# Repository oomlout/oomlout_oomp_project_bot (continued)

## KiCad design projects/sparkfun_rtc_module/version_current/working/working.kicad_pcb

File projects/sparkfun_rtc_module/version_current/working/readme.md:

# RTC-Module by sparkfun  
This is a harvested standardized copy of a project from github.  
The original project can be found at:  
https://github.com/sparkfun/RTC-Module  
Please consult that link for additional, details, files, and license information.  
Note: It was auto harvested and if the original repo had more than one board file or anything out of the ordinary the files here are likely not representative.

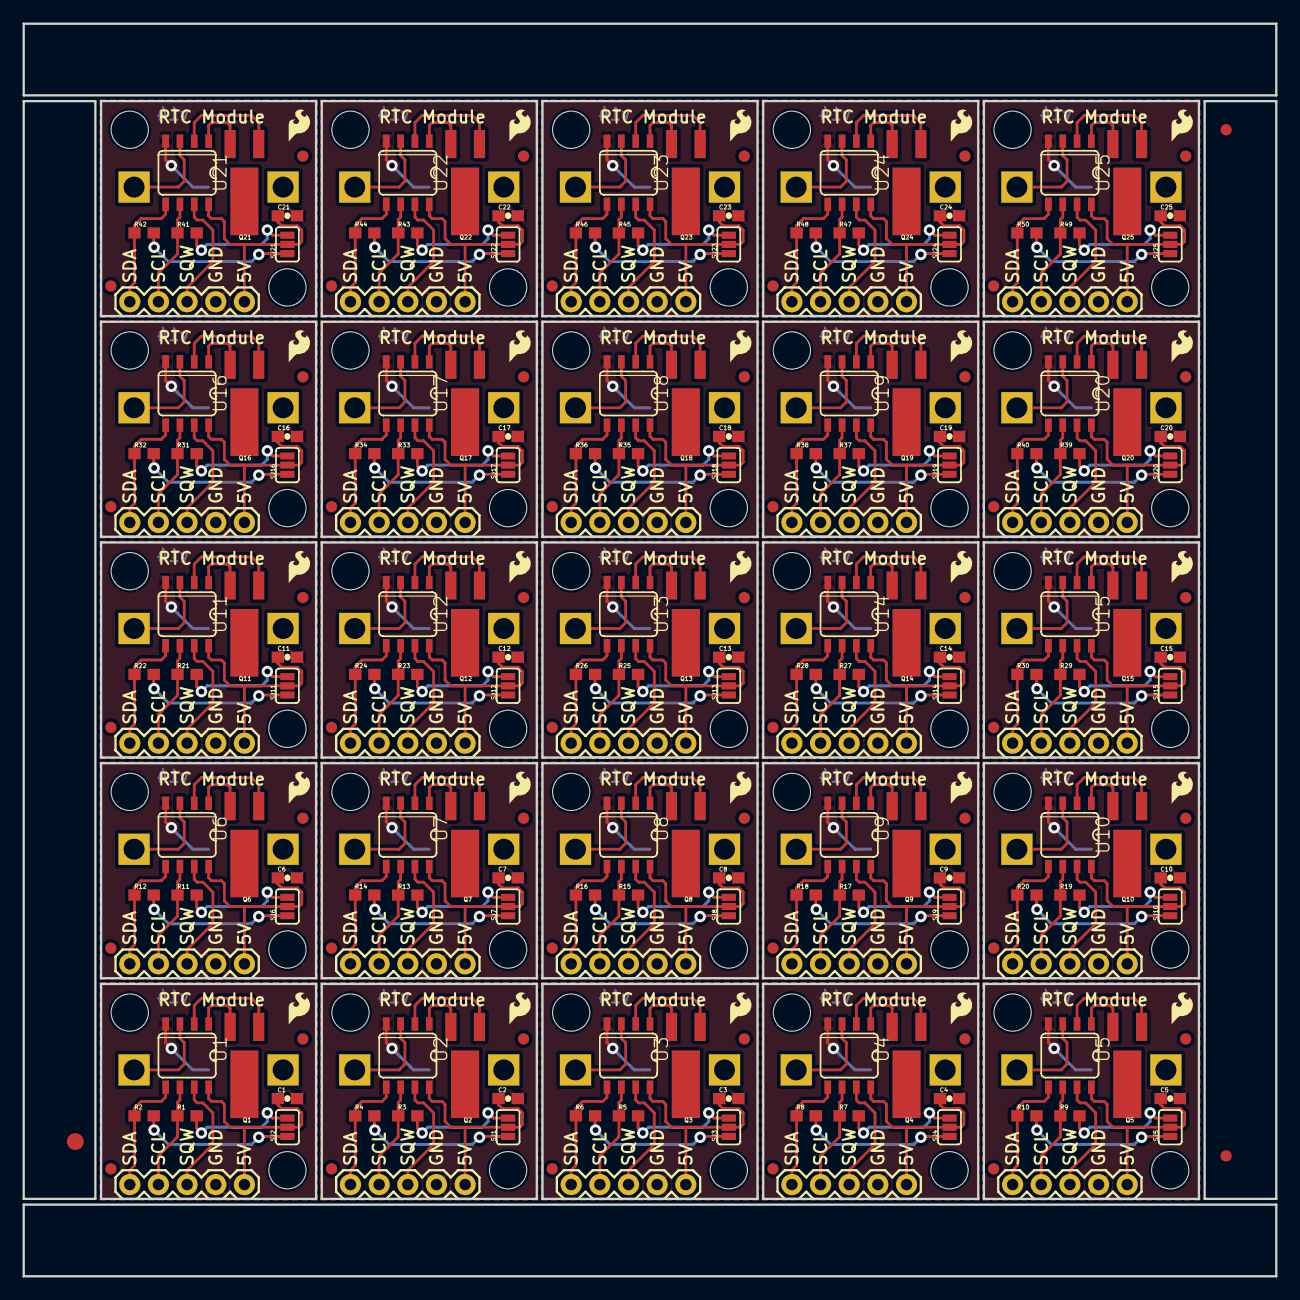
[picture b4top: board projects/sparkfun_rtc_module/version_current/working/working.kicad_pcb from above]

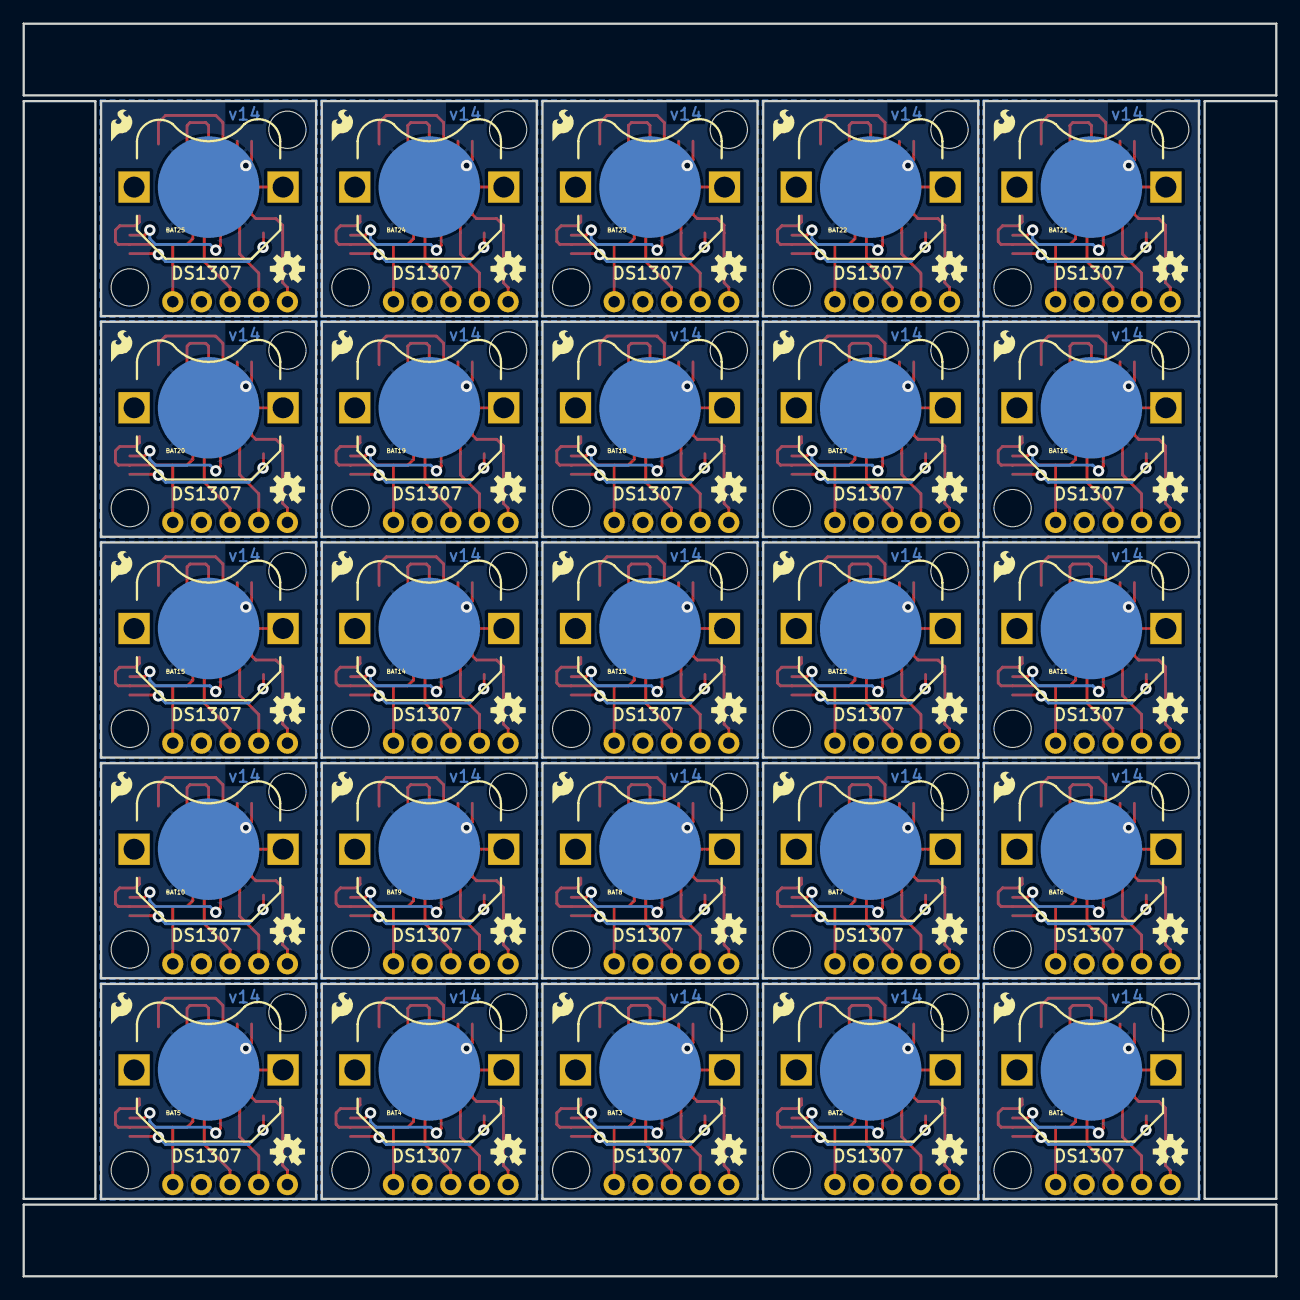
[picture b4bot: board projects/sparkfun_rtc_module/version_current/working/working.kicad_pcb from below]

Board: 2 copper layers, 111.0 x 111.0 mm, 378 parts (75 on the bottom side), 250 nets.

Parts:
BAT1, BAT2, BAT3, BAT4, BAT5, BAT6, BAT7, BAT8, BAT9, BAT10, BAT11, BAT12, BAT13, BAT14, BAT15, BAT16, BAT17, BAT18, BAT19, BAT20, BAT21, BAT22, BAT23, BAT24, BAT25: BATTCON_12MM_PTH
C1, C2, C3, C4, C5, C6, C7, C8, C9, C10, C11, C12, C13, C14, C15, C16, C17, C18, C19, C20, C21, C22, C23, C24, C25: 0.1uF; 0603-CAP
E$1, E$2, E$3, E$4, E$5, E$6, E$7, E$8, E$9, E$10, E$11, E$12, E$13, E$14, E$15, E$16, E$17, E$18, E$19, E$20, E$21, E$22, E$23, E$24, E$25, E$26, E$27, E$28, E$29, E$30, E$31, E$32, E$33, E$34, E$35, E$36, E$37, E$38, E$39, E$40, E$41, E$42, E$43, E$44, E$45, E$46, E$47, E$48, E$49, E$50, E$54, E$55: FIDUCIAL-1X2
E$51: FIDUCIAL-1.5X3
JP1, JP2, JP3, JP4, JP5, JP6, JP7, JP8, JP9, JP10, JP11, JP12, JP13, JP14, JP15, JP16, JP17, JP18, JP19, JP20, JP21, JP22, JP23, JP24, JP25: 1X05
LOGO1, LOGO2, LOGO3, LOGO4, LOGO5, LOGO6, LOGO7, LOGO8, LOGO9, LOGO10, LOGO11, LOGO12, LOGO13, LOGO14, LOGO15, LOGO16, LOGO17, LOGO18, LOGO19, LOGO20, LOGO21, LOGO22, LOGO23, LOGO24, LOGO25: OSHW-LOGOS; OSHW-LOGO-S
Q1, Q2, Q3, Q4, Q5, Q6, Q7, Q8, Q9, Q10, Q11, Q12, Q13, Q14, Q15, Q16, Q17, Q18, Q19, Q20, Q21, Q22, Q23, Q24, Q25: 32.768kHz; CRYSTAL-32KHZ-SMD
R1, R2, R3, R4, R5, R6, R7, R8, R9, R10, R11, R12, R13, R14, R15, R16, R17, R18, R19, R20, R21, R22, R23, R24, R25, R26, R27, R28, R29, R30, R31, R32, R33, R34, R35, R36, R37, R38, R39, R40, R41, R42, R43, R44, R45, R46, R47, R48, R49, R50: 4.7k; 0603
SJ1, SJ2, SJ3, SJ4, SJ5, SJ6, SJ7, SJ8, SJ9, SJ10, SJ11, SJ12, SJ13, SJ14, SJ15, SJ16, SJ17, SJ18, SJ19, SJ20, SJ21, SJ22, SJ23, SJ24, SJ25: SJ_3_PASTE1&2&3
U1, U2, U3, U4, U5, U6, U7, U8, U9, U10, U11, U12, U13, U14, U15, U16, U17, U18, U19, U20, U21, U22, U23, U24, U25: DS1307; SO08-TIGHT
U$1, U$2, U$3, U$8, U$9, U$12, U$13, U$16, U$17, U$20, U$21, U$24, U$25, U$28, U$29, U$32, U$33, U$36, U$37, U$40, U$41, U$44, U$45, U$48, U$49, U$52, U$53, U$56, U$57, U$60, U$61, U$64, U$65, U$68, U$69, U$72, U$73, U$76, U$77, U$80, U$81, U$84, U$85, U$88, U$89, U$92, U$93, U$96, U$97, U$100: LOGO-SFESK; SFE-LOGO-FLAME
U$4, U$5, U$6, U$7, U$10, U$11, U$14, U$15, U$18, U$19, U$22, U$23, U$26, U$27, U$30, U$31, U$34, U$35, U$38, U$39, U$42, U$43, U$46, U$47, U$50, U$51, U$54, U$55, U$58, U$59, U$62, U$63, U$66, U$67, U$70, U$71, U$74, U$75, U$78, U$79, U$82, U$83, U$86, U$87, U$90, U$91, U$94, U$95, U$98, U$99: STAND-OFF

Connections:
5V: C1.1, JP1.1, SJ2.2, U1.8
5V1: C2.1, JP2.1, SJ1.2, U2.8
5V2: C3.1, JP3.1, SJ3.2, U3.8
5V3: C4.1, JP4.1, SJ4.2, U4.8
5V4: C5.1, JP5.1, SJ5.2, U5.8
5V5: C6.1, JP6.1, SJ6.2, U6.8
5V6: C7.1, JP7.1, SJ7.2, U7.8
5V7: C8.1, JP8.1, SJ8.2, U8.8
5V8: C9.1, JP9.1, SJ9.2, U9.8
5V9: C10.1, JP10.1, SJ10.2, U10.8
5V10: C11.1, JP11.1, SJ11.2, U11.8
5V11: C12.1, JP12.1, SJ12.2, U12.8
5V12: C13.1, JP13.1, SJ13.2, U13.8
5V13: C14.1, JP14.1, SJ14.2, U14.8
5V14: C15.1, JP15.1, SJ15.2, U15.8
5V15: C16.1, JP16.1, SJ16.2, U16.8
5V16: C17.1, JP17.1, SJ17.2, U17.8
5V17: C18.1, JP18.1, SJ18.2, U18.8
5V18: C19.1, JP19.1, SJ19.2, U19.8
5V19: C20.1, JP20.1, SJ20.2, U20.8
5V20: C21.1, JP21.1, SJ21.2, U21.8
5V21: C22.1, JP22.1, SJ22.2, U22.8
5V22: C23.1, JP23.1, SJ23.2, U23.8
5V23: C24.1, JP24.1, SJ24.2, U24.8
5V24: C25.1, JP25.1, SJ25.2, U25.8
GND: BAT1.GND, C1.2, JP1.2, U1.4
GND1: BAT2.GND, C2.2, JP2.2, U2.4
GND2: BAT3.GND, C3.2, JP3.2, U3.4
GND3: BAT4.GND, C4.2, JP4.2, U4.4
GND4: BAT5.GND, C5.2, JP5.2, U5.4
GND5: BAT6.GND, C6.2, JP6.2, U6.4
GND6: BAT7.GND, C7.2, JP7.2, U7.4
GND7: BAT8.GND, C8.2, JP8.2, U8.4
GND8: BAT9.GND, C9.2, JP9.2, U9.4
GND9: BAT10.GND, C10.2, JP10.2, U10.4
GND10: BAT11.GND, C11.2, JP11.2, U11.4
GND11: BAT12.GND, C12.2, JP12.2, U12.4
GND12: BAT13.GND, C13.2, JP13.2, U13.4
GND13: BAT14.GND, C14.2, JP14.2, U14.4
GND14: BAT15.GND, C15.2, JP15.2, U15.4
GND15: BAT16.GND, C16.2, JP16.2, U16.4
GND16: BAT17.GND, C17.2, JP17.2, U17.4
GND17: BAT18.GND, C18.2, JP18.2, U18.4
GND18: BAT19.GND, C19.2, JP19.2, U19.4
GND19: BAT20.GND, C20.2, JP20.2, U20.4
GND20: BAT21.GND, C21.2, JP21.2, U21.4
GND21: BAT22.GND, C22.2, JP22.2, U22.4
GND22: BAT23.GND, C23.2, JP23.2, U23.4
GND23: BAT24.GND, C24.2, JP24.2, U24.4
GND24: BAT25.GND, C25.2, JP25.2, U25.4
unnamed: Q1.X2, U1.1
unnamed: Q1.X1, U1.2
unnamed: Q2.X2, U2.1
unnamed: BAT1.VCC@1, U1.3
unnamed: R1.2, SJ2.3
unnamed: R2.2, SJ2.1
unnamed: Q2.X1, U2.2
unnamed: BAT2.VCC@1, U2.3
unnamed: R3.2, SJ1.3
unnamed: R4.2, SJ1.1
unnamed: Q3.X2, U3.1
unnamed: Q3.X1, U3.2
unnamed: BAT3.VCC@1, U3.3
unnamed: R5.2, SJ3.3
unnamed: R6.2, SJ3.1
unnamed: Q4.X2, U4.1
unnamed: Q4.X1, U4.2
unnamed: BAT4.VCC@1, U4.3
unnamed: R7.2, SJ4.3
unnamed: R8.2, SJ4.1
unnamed: Q5.X2, U5.1
unnamed: Q5.X1, U5.2
unnamed: BAT5.VCC@1, U5.3
unnamed: R9.2, SJ5.3
unnamed: R10.2, SJ5.1
unnamed: Q6.X2, U6.1
unnamed: Q6.X1, U6.2
unnamed: BAT6.VCC@1, U6.3
unnamed: R11.2, SJ6.3
unnamed: R12.2, SJ6.1
unnamed: Q7.X2, U7.1
unnamed: Q7.X1, U7.2
unnamed: BAT7.VCC@1, U7.3
unnamed: R13.2, SJ7.3
unnamed: R14.2, SJ7.1
unnamed: Q8.X2, U8.1
unnamed: Q8.X1, U8.2
unnamed: BAT8.VCC@1, U8.3
unnamed: R15.2, SJ8.3
unnamed: R16.2, SJ8.1
unnamed: Q9.X2, U9.1
unnamed: Q9.X1, U9.2
unnamed: BAT9.VCC@1, U9.3
unnamed: R17.2, SJ9.3
unnamed: R18.2, SJ9.1
unnamed: Q10.X2, U10.1
unnamed: Q10.X1, U10.2
unnamed: BAT10.VCC@1, U10.3
unnamed: R19.2, SJ10.3
unnamed: R20.2, SJ10.1
unnamed: Q11.X2, U11.1
unnamed: Q11.X1, U11.2
unnamed: BAT11.VCC@1, U11.3
unnamed: R21.2, SJ11.3
unnamed: R22.2, SJ11.1
unnamed: Q12.X2, U12.1
unnamed: Q12.X1, U12.2
unnamed: BAT12.VCC@1, U12.3
unnamed: R23.2, SJ12.3
unnamed: R24.2, SJ12.1
unnamed: Q13.X2, U13.1
unnamed: Q13.X1, U13.2
unnamed: BAT13.VCC@1, U13.3
unnamed: R25.2, SJ13.3
unnamed: R26.2, SJ13.1
unnamed: Q14.X2, U14.1
unnamed: Q14.X1, U14.2
unnamed: BAT14.VCC@1, U14.3
unnamed: R27.2, SJ14.3
unnamed: R28.2, SJ14.1
unnamed: Q15.X2, U15.1
unnamed: Q15.X1, U15.2
unnamed: BAT15.VCC@1, U15.3
unnamed: R29.2, SJ15.3
unnamed: R30.2, SJ15.1
unnamed: Q16.X2, U16.1
unnamed: Q16.X1, U16.2
unnamed: BAT16.VCC@1, U16.3
unnamed: R31.2, SJ16.3
unnamed: R32.2, SJ16.1
unnamed: Q17.X2, U17.1
unnamed: Q17.X1, U17.2
unnamed: BAT17.VCC@1, U17.3
unnamed: R33.2, SJ17.3
unnamed: R34.2, SJ17.1
unnamed: Q18.X2, U18.1
unnamed: Q18.X1, U18.2
unnamed: BAT18.VCC@1, U18.3
unnamed: R35.2, SJ18.3
unnamed: R36.2, SJ18.1
unnamed: Q19.X2, U19.1
unnamed: Q19.X1, U19.2
unnamed: BAT19.VCC@1, U19.3
unnamed: R37.2, SJ19.3
unnamed: R38.2, SJ19.1
unnamed: Q20.X2, U20.1
unnamed: Q20.X1, U20.2
unnamed: BAT20.VCC@1, U20.3
unnamed: R39.2, SJ20.3
unnamed: R40.2, SJ20.1
unnamed: Q21.X2, U21.1
unnamed: Q21.X1, U21.2
unnamed: BAT21.VCC@1, U21.3
unnamed: R41.2, SJ21.3
unnamed: R42.2, SJ21.1
unnamed: Q22.X2, U22.1
unnamed: Q22.X1, U22.2
unnamed: BAT22.VCC@1, U22.3
unnamed: R43.2, SJ22.3
unnamed: R44.2, SJ22.1
unnamed: Q23.X2, U23.1
unnamed: Q23.X1, U23.2
unnamed: BAT23.VCC@1, U23.3
unnamed: R45.2, SJ23.3
unnamed: R46.2, SJ23.1
unnamed: Q24.X2, U24.1
unnamed: Q24.X1, U24.2
unnamed: BAT24.VCC@1, U24.3
unnamed: R47.2, SJ24.3
unnamed: R48.2, SJ24.1
unnamed: Q25.X2, U25.1
unnamed: Q25.X1, U25.2
unnamed: BAT25.VCC@1, U25.3
unnamed: R49.2, SJ25.3
unnamed: R50.2, SJ25.1
SCL: JP1.4, R1.1, U1.6
SCL1: JP2.4, R3.1, U2.6
SCL2: JP3.4, R5.1, U3.6
SCL3: JP4.4, R7.1, U4.6
SCL4: JP5.4, R9.1, U5.6
SCL5: JP6.4, R11.1, U6.6
SCL6: JP7.4, R13.1, U7.6
SCL7: JP8.4, R15.1, U8.6
SCL8: JP9.4, R17.1, U9.6
SCL9: JP10.4, R19.1, U10.6
SCL10: JP11.4, R21.1, U11.6
SCL11: JP12.4, R23.1, U12.6
SCL12: JP13.4, R25.1, U13.6
SCL13: JP14.4, R27.1, U14.6
SCL14: JP15.4, R29.1, U15.6
SCL15: JP16.4, R31.1, U16.6
SCL16: JP17.4, R33.1, U17.6
SCL17: JP18.4, R35.1, U18.6
SCL18: JP19.4, R37.1, U19.6
SCL19: JP20.4, R39.1, U20.6
SCL20: JP21.4, R41.1, U21.6
SCL21: JP22.4, R43.1, U22.6
SCL22: JP23.4, R45.1, U23.6
SCL23: JP24.4, R47.1, U24.6
SCL24: JP25.4, R49.1, U25.6
SDA: JP1.5, R2.1, U1.5
SDA1: JP2.5, R4.1, U2.5
SDA2: JP3.5, R6.1, U3.5
SDA3: JP4.5, R8.1, U4.5
SDA4: JP5.5, R10.1, U5.5
SDA5: JP6.5, R12.1, U6.5
SDA6: JP7.5, R14.1, U7.5
SDA7: JP8.5, R16.1, U8.5
SDA8: JP9.5, R18.1, U9.5
SDA9: JP10.5, R20.1, U10.5
SDA10: JP11.5, R22.1, U11.5
SDA11: JP12.5, R24.1, U12.5
SDA12: JP13.5, R26.1, U13.5
SDA13: JP14.5, R28.1, U14.5
SDA14: JP15.5, R30.1, U15.5
SDA15: JP16.5, R32.1, U16.5
SDA16: JP17.5, R34.1, U17.5
SDA17: JP18.5, R36.1, U18.5
SDA18: JP19.5, R38.1, U19.5
SDA19: JP20.5, R40.1, U20.5
SDA20: JP21.5, R42.1, U21.5
SDA21: JP22.5, R44.1, U22.5
SDA22: JP23.5, R46.1, U23.5
SDA23: JP24.5, R48.1, U24.5
SDA24: JP25.5, R50.1, U25.5
SQW: JP1.3, U1.7
SQW1: JP2.3, U2.7
SQW2: JP3.3, U3.7
SQW3: JP4.3, U4.7
SQW4: JP5.3, U5.7
SQW5: JP6.3, U6.7
SQW6: JP7.3, U7.7
SQW7: JP8.3, U8.7
SQW8: JP9.3, U9.7
SQW9: JP10.3, U10.7
SQW10: JP11.3, U11.7
SQW11: JP12.3, U12.7
SQW12: JP13.3, U13.7
SQW13: JP14.3, U14.7
SQW14: JP15.3, U15.7
SQW15: JP16.3, U16.7
SQW16: JP17.3, U17.7
SQW17: JP18.3, U18.7
SQW18: JP19.3, U19.7
SQW19: JP20.3, U20.7
SQW20: JP21.3, U21.7
SQW21: JP22.3, U22.7
SQW22: JP23.3, U23.7
SQW23: JP24.3, U24.7
SQW24: JP25.3, U25.7

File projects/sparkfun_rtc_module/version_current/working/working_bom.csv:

"Id";"Designator";"Footprint";"Quantity";"Designation";"Supplier and ref";
1;"U$22,U$90,U$50,U$86,U$66,U$83,U$62,U$30,U$63,U$38,U$67,U$95,U$6,U$79,U$11,U$42,U$94,U$4,U$71,U$5,U$99,U$58,U$98,U$46,U$91,U$27,U$59,U$31,U$54,U$7,U$82,U$70,U$47,U$51,U$74,U$10,U$15,U$23,U$78,U$14,U$75,U$18,U$26,U$34,U$55,U$43,U$39,U$35,U$19,U$87";"STAND-OFF";50;"STAND-OFF";;;
2;"U$89,U$49,U$73,U$17,U$61,U$41,U$1,U$9,U$13,U$81,U$21,U$85,U$33,U$53,U$3,U$93,U$25,U$37,U$45,U$29,U$57,U$69,U$97,U$65,U$77,U$56,U$40,U$20,U$96,U$52,U$32,U$8,U$72,U$88,U$12,U$48,U$76,U$60,U$16,U$68,U$36,U$24,U$44,U$64,U$92,U$80,U$28,U$100,U$84,U$2";"SFE-LOGO-FLAME";50;"LOGO-SFESK";;;
3;"E$40,E$26,E$17,E$46,E$4,E$12,E$6,E$14,E$24,E$22,E$11,E$33,E$10,E$38,E$31,E$19,E$36,E$37,E$5,E$49,E$43,E$2,E$29,E$16,E$15,E$7,E$1,E$47,E$48,E$34,E$32,E$50,E$30,E$55,E$54,E$21,E$9,E$27,E$20,E$35,E$45,E$41,E$8,E$13,E$25,E$28,E$3,E$39,E$44,E$42,E$18,E$23";"FIDUCIAL-1X2";52;"";;;
4;"C4,C11,C24,C18,C12,C10,C22,C7,C15,C3,C25,C6,C16,C23,C13,C2,C19,C17,C14,C8,C1,C20,C9,C5,C21";"0603-CAP";25;"0.1uF";;;
5;"R40,R6,R29,R39,R4,R13,R33,R36,R28,R50,R19,R43,R11,R15,R26,R1,R20,R45,R8,R49,R3,R22,R35,R30,R47,R44,R18,R5,R16,R10,R7,R2,R46,R32,R48,R42,R12,R14,R9,R24,R23,R21,R31,R27,R41,R34,R17,R37,R25,R38";"0603";50;"4.7k";;;
6;"U16,U25,U23,U24,U4,U7,U1,U21,U17,U8,U15,U10,U22,U12,U11,U14,U6,U5,U18,U3,U20,U13,U2,U9,U19";"SO08-TIGHT";25;"DS1307";;;
7;"Q11,Q16,Q25,Q14,Q10,Q21,Q20,Q6,Q19,Q24,Q15,Q9,Q7,Q13,Q3,Q5,Q12,Q22,Q2,Q23,Q4,Q17,Q1,Q18,Q8";"CRYSTAL-32KHZ-SMD";25;"32.768kHz";;;
8;"JP9,JP11,JP7,JP19,JP23,JP13,JP8,JP1,JP3,JP6,JP18,JP5,JP17,JP10,JP4,JP16,JP25,JP14,JP22,JP15,JP24,JP2,JP21,JP20,JP12";"1X05";25;"";;;
9;"SJ9,SJ1,SJ19,SJ24,SJ6,SJ18,SJ3,SJ12,SJ11,SJ25,SJ21,SJ14,SJ5,SJ10,SJ20,SJ23,SJ4,SJ17,SJ15,SJ13,SJ22,SJ2,SJ7,SJ8,SJ16";"SJ_3_PASTE1&2&3";25;"";;;
10;"E$51";"FIDUCIAL-1.5X3";1;"";;;
11;"LOGO21,LOGO15,LOGO23,LOGO1,LOGO9,LOGO17,LOGO7,LOGO10,LOGO16,LOGO4,LOGO18,LOGO5,LOGO25,LOGO6,LOGO24,LOGO2,LOGO12,LOGO11,LOGO8,LOGO19,LOGO13,LOGO20,LOGO3,LOGO14,LOGO22";"OSHW-LOGO-S";25;"OSHW-LOGOS";;;
12;"BAT18,BAT13,BAT1,BAT23,BAT5,BAT10,BAT17,BAT15,BAT19,BAT24,BAT12,BAT7,BAT4,BAT25,BAT16,BAT9,BAT3,BAT6,BAT20,BAT2,BAT21,BAT11,BAT22,BAT8,BAT14";"BATTCON_12MM_PTH";25;"";;;

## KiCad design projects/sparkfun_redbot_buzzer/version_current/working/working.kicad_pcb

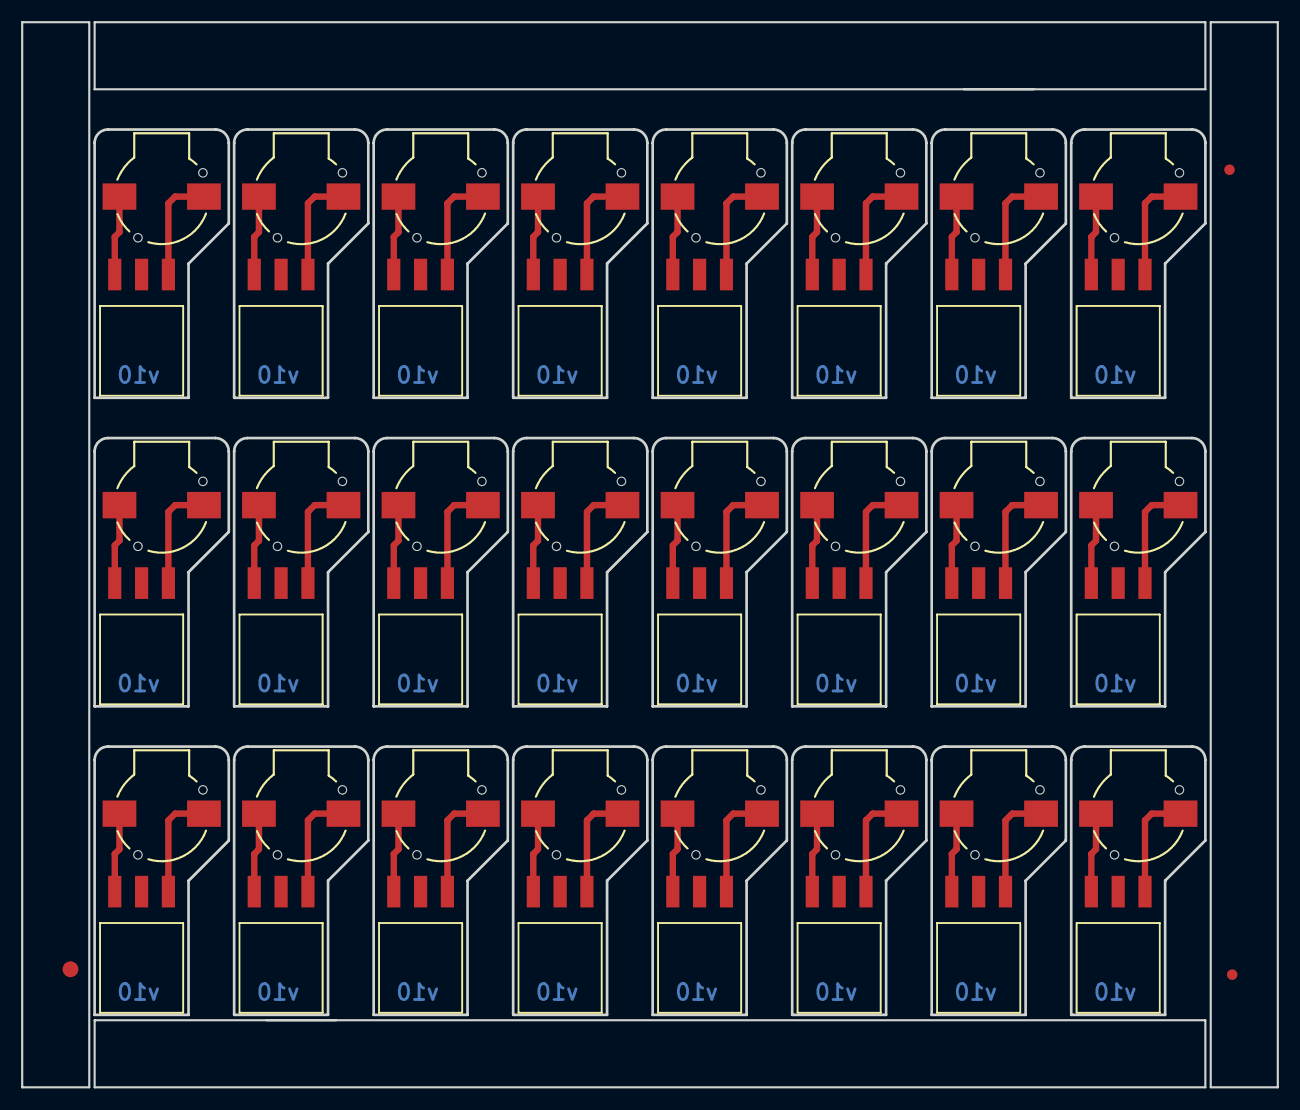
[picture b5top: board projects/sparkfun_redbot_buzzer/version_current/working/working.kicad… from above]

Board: 4 copper layers, 118.9 x 100.8 mm, 99 parts (48 on the bottom side), 48 nets.

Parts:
B1, B2, B3, B4, B5, B6, B7, B8, B9, B10, B11, B12, B13, B14, B15, B16, B17, B18, B19, B20, B21, B22, B23, B24: Buzzer; BUZZER-CCV
E$1: FIDUCIAL-1.5X3
E$4, E$5: FIDUCIAL-1X2
JP1, JP2, JP3, JP4, JP5, JP6, JP7, JP8, JP9, JP10, JP11, JP12, JP13, JP14, JP15, JP16, JP17, JP18, JP19, JP20, JP21, JP22, JP23, JP24: 1x3 RA Female .1"; 1X03_SMD_RA_FEMALE
LOGO1, LOGO3, LOGO5, LOGO7, LOGO9, LOGO11, LOGO13, LOGO15, LOGO17, LOGO19, LOGO21, LOGO23, LOGO25, LOGO27, LOGO29, LOGO31, LOGO33, LOGO35, LOGO37, LOGO39, LOGO41, LOGO43, LOGO45, LOGO47: OSHW-LOGOS; OSHW-LOGO-S
LOGO2, LOGO4, LOGO6, LOGO8, LOGO10, LOGO12, LOGO14, LOGO16, LOGO18, LOGO20, LOGO22, LOGO24, LOGO26, LOGO28, LOGO30, LOGO32, LOGO34, LOGO36, LOGO38, LOGO40, LOGO42, LOGO44, LOGO46, LOGO48: SFE_LOGO_NAME_FLAME.1_INCH; SFE_LOGO_NAME_FLAME_.1

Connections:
unnamed: B1.+, JP1.1
unnamed: B1.-, JP1.3
unnamed: B2.-, JP2.3
unnamed: B2.+, JP2.1
unnamed: B3.-, JP3.3
unnamed: B3.+, JP3.1
unnamed: B4.-, JP4.3
unnamed: B4.+, JP4.1
unnamed: B5.-, JP5.3
unnamed: B5.+, JP5.1
unnamed: B6.-, JP6.3
unnamed: B6.+, JP6.1
unnamed: B7.-, JP7.3
unnamed: B7.+, JP7.1
unnamed: B8.-, JP8.3
unnamed: B8.+, JP8.1
unnamed: B9.-, JP9.3
unnamed: B9.+, JP9.1
unnamed: B10.-, JP10.3
unnamed: B10.+, JP10.1
unnamed: B11.-, JP11.3
unnamed: B11.+, JP11.1
unnamed: B12.-, JP12.3
unnamed: B12.+, JP12.1
unnamed: B13.-, JP13.3
unnamed: B13.+, JP13.1
unnamed: B14.-, JP14.3
unnamed: B14.+, JP14.1
unnamed: B15.-, JP15.3
unnamed: B15.+, JP15.1
unnamed: B16.-, JP16.3
unnamed: B16.+, JP16.1
unnamed: B17.-, JP17.3
unnamed: B17.+, JP17.1
unnamed: B18.-, JP18.3
unnamed: B18.+, JP18.1
unnamed: B19.-, JP19.3
unnamed: B19.+, JP19.1
unnamed: B20.-, JP20.3
unnamed: B20.+, JP20.1
unnamed: B21.-, JP21.3
unnamed: B21.+, JP21.1
unnamed: B22.-, JP22.3
unnamed: B22.+, JP22.1
unnamed: B23.-, JP23.3
unnamed: B23.+, JP23.1
unnamed: B24.-, JP24.3
unnamed: B24.+, JP24.1

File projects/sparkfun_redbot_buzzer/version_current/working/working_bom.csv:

"Id";"Designator";"Footprint";"Quantity";"Designation";"Supplier and ref";
1;"E$1";"FIDUCIAL-1.5X3";1;"";;;
2;"JP7,JP9,JP24,JP13,JP15,JP19,JP6,JP16,JP3,JP10,JP12,JP4,JP18,JP21,JP20,JP17,JP2,JP8,JP1,JP11,JP5,JP14,JP23,JP22";"1X03_SMD_RA_FEMALE";24;"1x3 RA Female .1"";;;
3;"B20,B13,B23,B11,B19,B6,B17,B15,B18,B24,B12,B22,B21,B10,B14,B5,B16,B3,B2,B4,B7,B1,B8,B9";"BUZZER-CCV";24;"Buzzer";;;
4;"E$5,E$4";"FIDUCIAL-1X2";2;"";;;
5;"LOGO40,LOGO6,LOGO36,LOGO14,LOGO32,LOGO30,LOGO28,LOGO20,LOGO34,LOGO18,LOGO12,LOGO44,LOGO22,LOGO10,LOGO24,LOGO38,LOGO46,LOGO8,LOGO16,LOGO2,LOGO42,LOGO4,LOGO48,LOGO26";"SFE_LOGO_NAME_FLAME_.1";24;"SFE_LOGO_NAME_FLAME.1_INCH";;;
6;"LOGO45,LOGO43,LOGO27,LOGO33,LOGO31,LOGO3,LOGO19,LOGO1,LOGO17,LOGO7,LOGO25,LOGO41,LOGO13,LOGO39,LOGO15,LOGO37,LOGO11,LOGO29,LOGO5,LOGO35,LOGO21,LOGO9,LOGO23,LOGO47";"OSHW-LOGO-S";24;"OSHW-LOGOS";;;

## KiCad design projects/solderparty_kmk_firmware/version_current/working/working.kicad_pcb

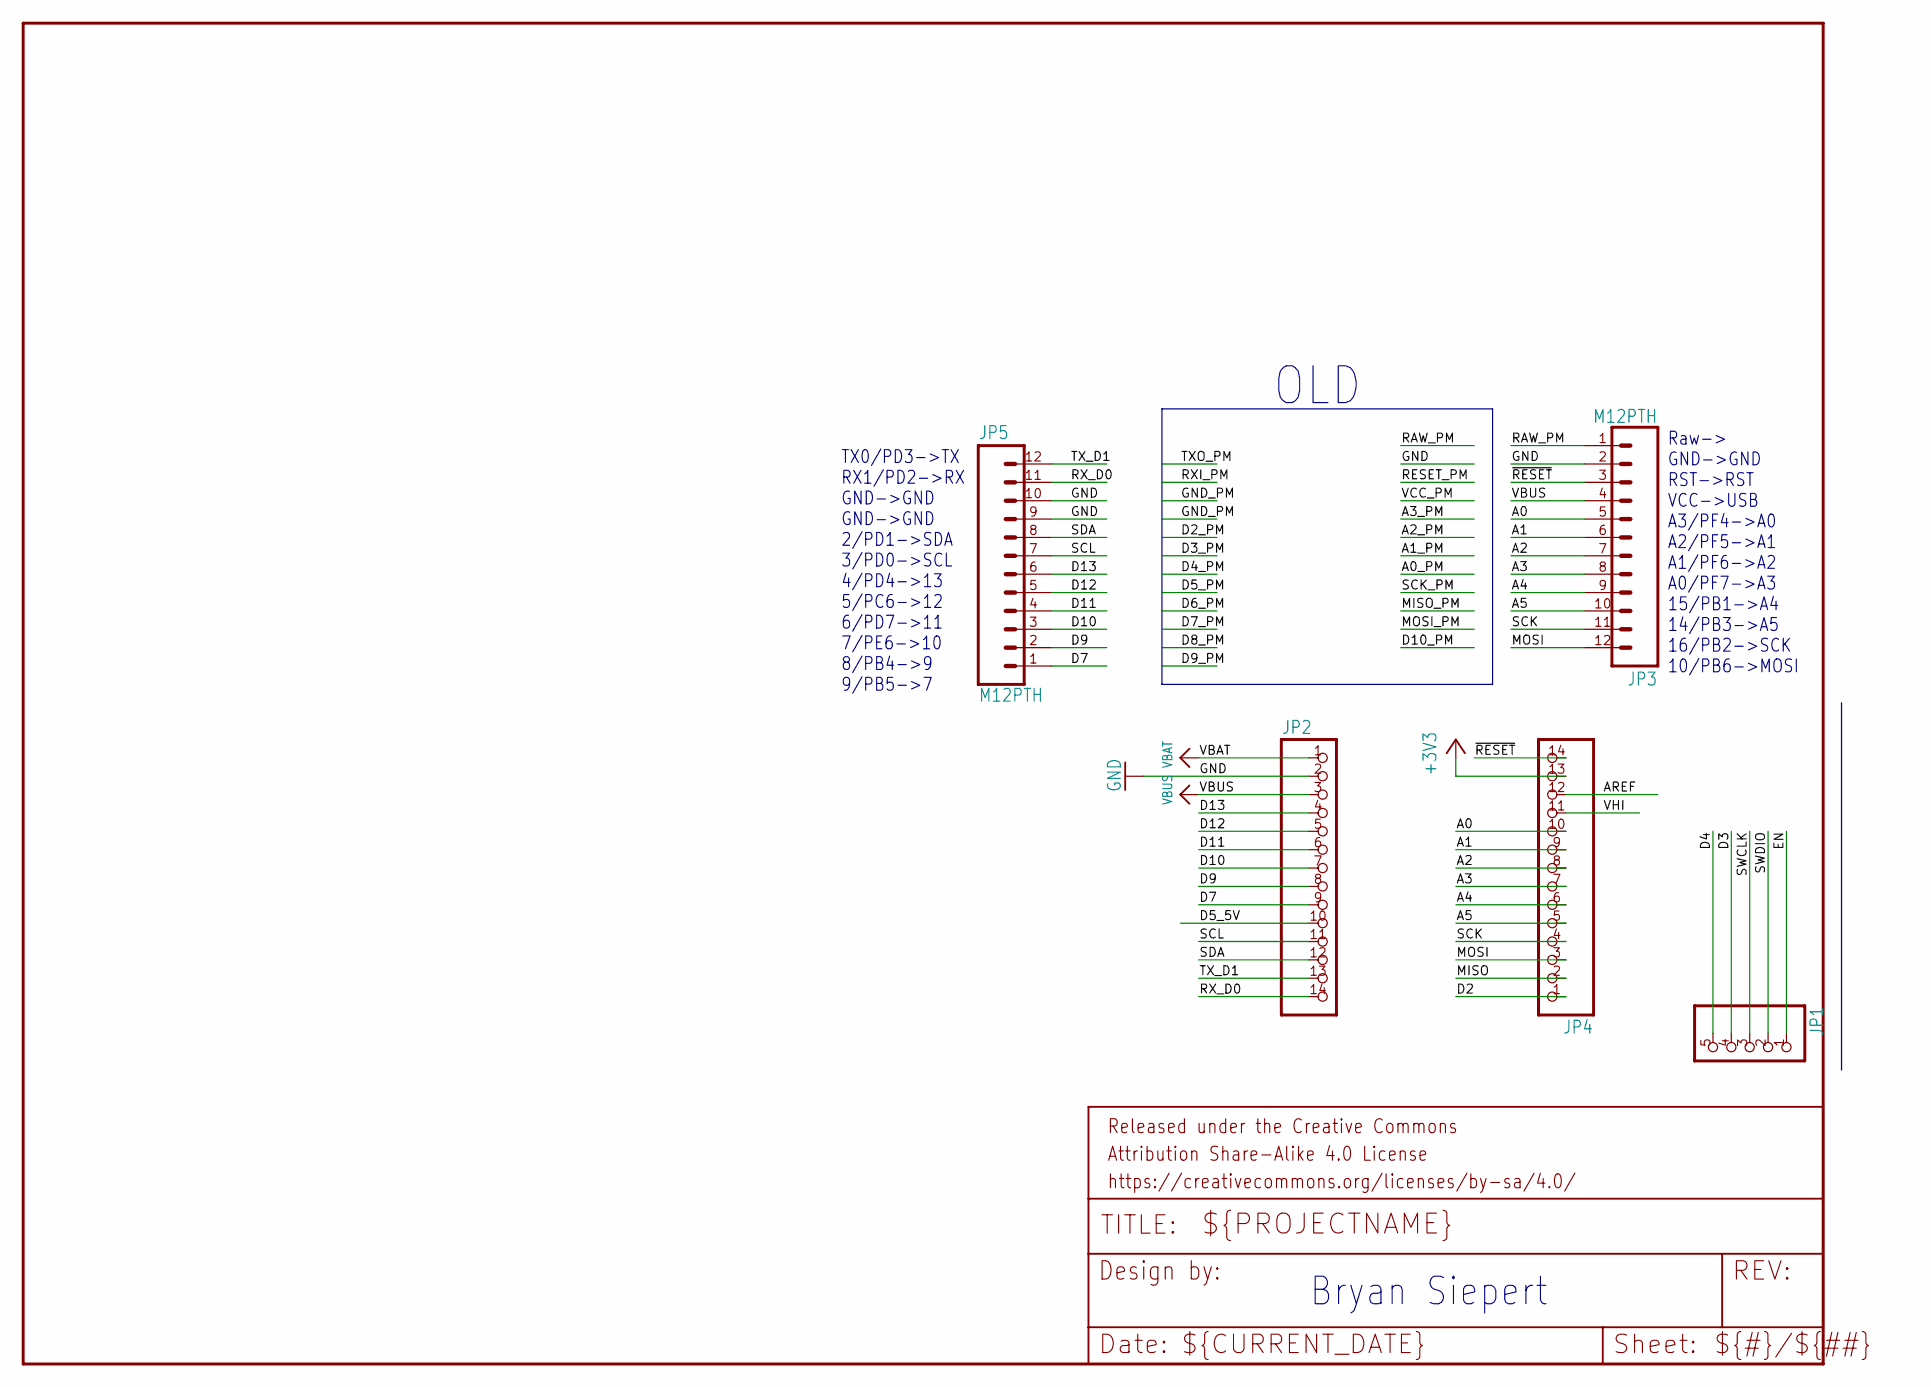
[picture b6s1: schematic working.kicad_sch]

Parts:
FRAME2: FRAME-LETTER; CREATIVE_COMMONS
JP1: HEADER-1X570MIL; 1X05_ROUND_70
JP2, JP4: HEADER-1X14; 1X14_ROUND70
JP3, JP5: M12PTH; 1X12

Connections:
+3V3: JP4.13
A0: JP3.5, JP4.10
A1: JP3.6, JP4.9
A2: JP3.7, JP4.8
A3: JP3.8, JP4.7
A4: JP3.9, JP4.6
A5: JP3.10, JP4.5
AREF: JP4.12
D2: JP4.1
D3: JP1.4
D4: JP1.5
D5_5V: JP2.10
D7: JP2.9, JP5.1
D9: JP2.8, JP5.2
D10: JP2.7, JP5.3
D11: JP2.6, JP5.4
D12: JP2.5, JP5.5
D13: JP2.4, JP5.6
EN: JP1.1
GND: JP2.2, JP3.2, JP5.9, JP5.10
MISO: JP4.2
MOSI: JP3.12, JP4.3
RAW_PM: JP3.1
RX_D0: JP2.14, JP5.11
SCK: JP3.11, JP4.4
SCL: JP2.11, JP5.7
SDA: JP2.12, JP5.8
SWCLK: JP1.3
SWDIO: JP1.2
TX_D1: JP2.13, JP5.12
VBAT: JP2.1
VBUS: JP2.3, JP3.4
VHI: JP4.11
~RESET: JP3.3, JP4.14

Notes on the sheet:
TX0/PD3->TX RX1/PD2->RX GND->GND GND->GND 2/PD1->SDA 3/PD0->SCL 4/PD4->13 5/PC6->12 6/PD7->11 7/PE6->10 8/PB4->9 9/PB5->7
Bryan Siepert
Raw-> GND->GND RST->RST VCC->USB A3/PF4->A0 A2/PF5->A1 A1/PF6->A2 A0/PF7->A3 15/PB1->A4 14/PB3->A5 16/PB2->SCK 10/PB6->MOSI
OLD

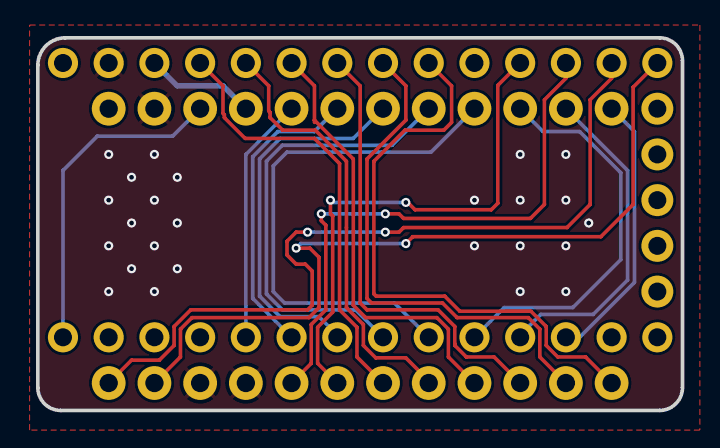
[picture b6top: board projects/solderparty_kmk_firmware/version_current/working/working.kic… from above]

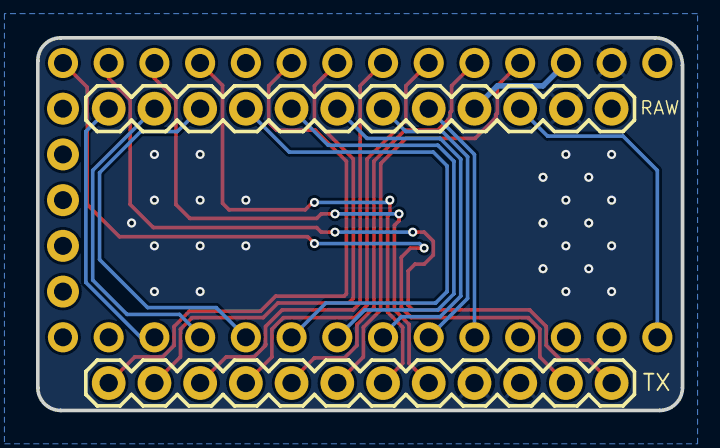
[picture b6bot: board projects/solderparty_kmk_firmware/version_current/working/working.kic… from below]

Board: 4 copper layers, 35.8 x 20.7 mm, 6 parts (2 on the bottom side), 21 nets.

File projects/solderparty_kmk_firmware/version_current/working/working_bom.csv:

"Id";"Designator";"Footprint";"Quantity";"Designation";"Supplier and ref";
1;"FRAME2";"CREATIVE_COMMONS";1;"FRAME-LETTER";;;
2;"JP1";"1X05_ROUND_70";1;"";;;
3;"JP4,JP2";"1X14_ROUND70";2;"";;;
4;"JP3,JP5";"1X12";2;"";;;

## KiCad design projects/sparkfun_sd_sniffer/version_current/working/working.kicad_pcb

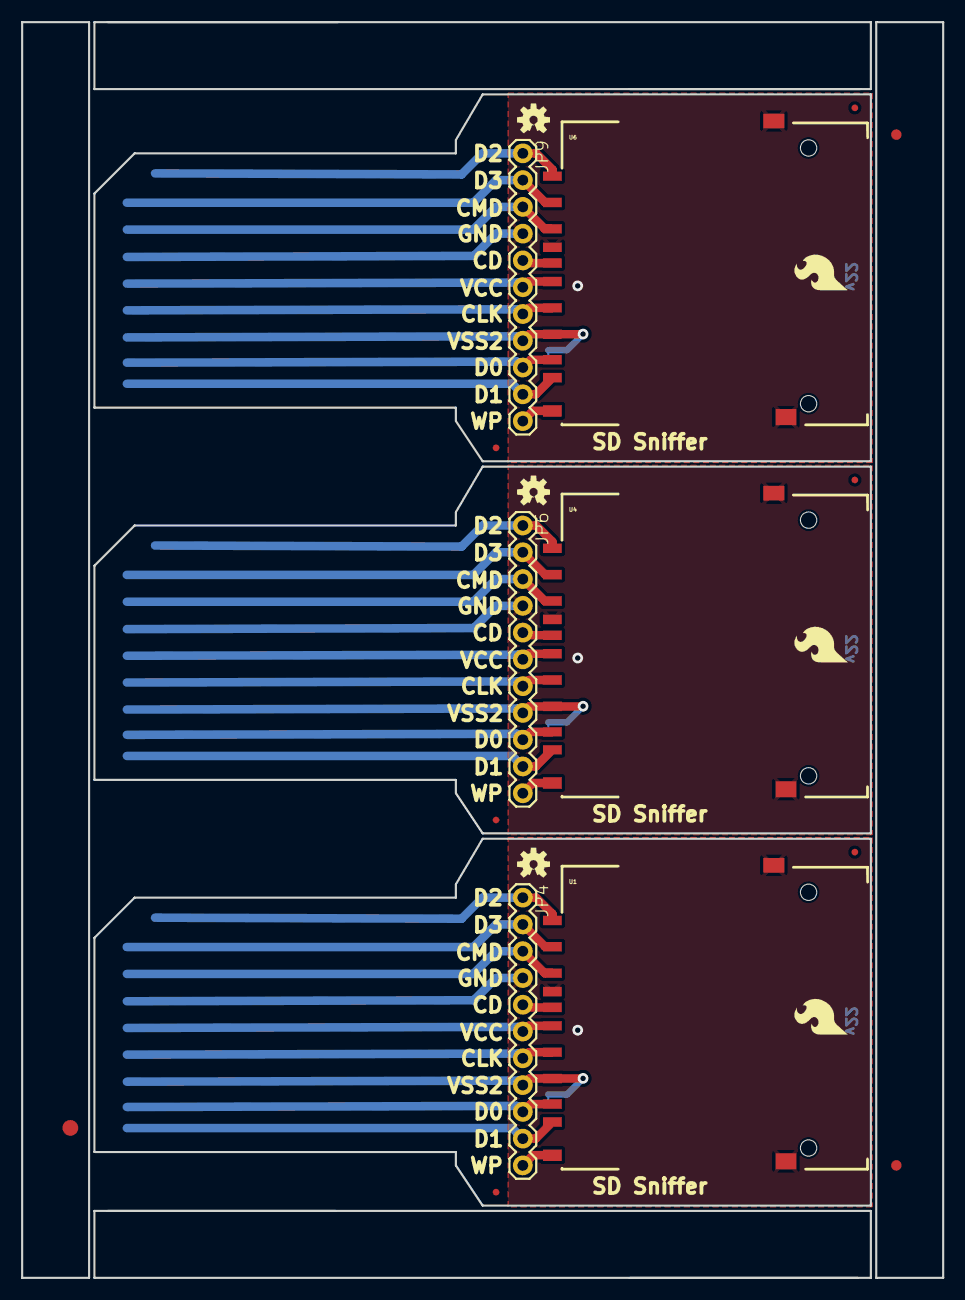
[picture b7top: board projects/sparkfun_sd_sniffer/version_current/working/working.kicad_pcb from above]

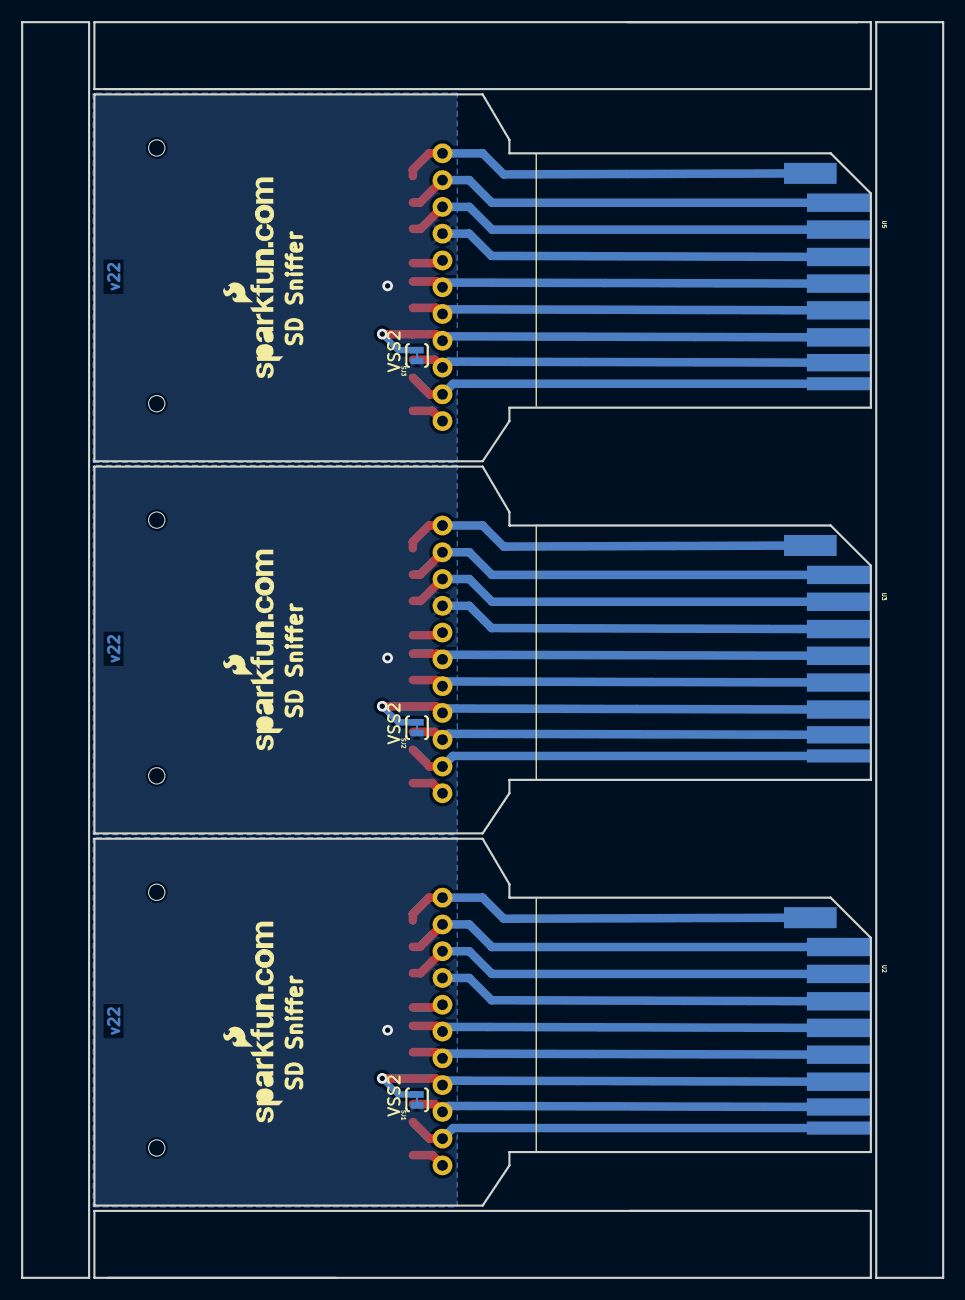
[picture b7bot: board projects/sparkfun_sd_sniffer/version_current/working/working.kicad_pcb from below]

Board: 2 copper layers, 87.4 x 119.1 mm, 30 parts (9 on the bottom side), 33 nets.

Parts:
E$1: FIDUCIAL-1.5X3
E$2, E$3: FIDUCIAL-1X2
JP1, JP2, JP3, JP5, JP7, JP8: FIDUCIALUFIDUCIAL; MICRO-FIDUCIAL
JP4, JP6, JP9: M11PTH; 1X11
LOGO0, LOGO1, LOGO2: LOGO-SFENEW; SFE-NEW-WEBLOGO
SJ1, SJ2, SJ3: SOLDERJUMPERTRACE; SJ_2S-TRACE
U1, U4, U6: SD_CARD_SOCKET; SD_1_1
U2, U3, U5: SD_MMC_CARDSD_PCB; SD-MMC-CARD
U$1, U$4, U$5: SFE_LOGO_FLAME.2_INCH; SFE_LOGO_FLAME_.2
U$2, U$3, U$6: OSHW-LOGOS; OSHW-LOGO-S

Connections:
CD: JP4.5, U1.CD
CD1: JP6.5, U4.CD
CD2: JP9.5, U6.CD
CLK: JP4.7, U1.5, U2.5
CLK1: JP6.7, U3.5, U4.5
CLK2: JP9.7, U5.5, U6.5
CMD: JP4.3, U1.2, U2.2
CMD1: JP6.3, U3.2, U4.2
CMD2: JP9.3, U5.2, U6.2
D0: JP4.9, U1.7, U2.7
D1: JP4.10, U1.8, U2.8
D2: JP4.1, U1.9, U2.9
D3: JP4.2, U1.1, U2.1
D4: JP6.1, U3.9, U4.9
D5: JP6.9, U3.7, U4.7
D6: JP6.10, U3.8, U4.8
D7: JP6.2, U3.1, U4.1
D8: JP9.1, U5.9, U6.9
D9: JP9.9, U5.7, U6.7
D10: JP9.10, U5.8, U6.8
D11: JP9.2, U5.1, U6.1
GND: JP4.4, SJ1.1, U1.3, U1.SH@1, U1.SH@2, U2.3
GND1: JP6.4, SJ2.1, U3.3, U4.3, U4.SH@1, U4.SH@2
GND2: JP9.4, SJ3.1, U5.3, U6.3, U6.SH@1, U6.SH@2
VCC: JP4.6, U1.4, U2.4
VCC1: JP6.6, U3.4, U4.4
VCC2: JP9.6, U5.4, U6.4
VSS1: JP6.8, SJ2.2, U3.6, U4.6
VSS2: JP4.8, SJ1.2, U1.6, U2.6
VSS3: JP9.8, SJ3.2, U5.6, U6.6
WP: JP4.11, U1.WP
WP1: JP6.11, U4.WP
WP2: JP9.11, U6.WP

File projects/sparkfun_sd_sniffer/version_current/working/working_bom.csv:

"Id";"Designator";"Footprint";"Quantity";"Designation";"Supplier and ref";
1;"U$1,U$5,U$4";"SFE_LOGO_FLAME_.2";3;"SFE_LOGO_FLAME.2_INCH";;;
2;"U$6,U$3,U$2";"OSHW-LOGO-S";3;"OSHW-LOGOS";;;
3;"JP3,JP1,JP5,JP7,JP8,JP2";"MICRO-FIDUCIAL";6;"FIDUCIALUFIDUCIAL";;;
4;"U6,U1,U4";"SD_1_1";3;"SD_CARD_SOCKET";;;
5;"E$2,E$3";"FIDUCIAL-1X2";2;"";;;
6;"JP9,JP4,JP6";"1X11";3;"M11PTH";;;
7;"E$1";"FIDUCIAL-1.5X3";1;"";;;
8;"U3,U2,U5";"SD-MMC-CARD";3;"SD_MMC_CARDSD_PCB";;;
9;"LOGO0,LOGO1,LOGO2";"SFE-NEW-WEBLOGO";3;"LOGO-SFENEW";;;
10;"SJ1,SJ2,SJ3";"SJ_2S-TRACE";3;"SOLDERJUMPERTRACE";;;
